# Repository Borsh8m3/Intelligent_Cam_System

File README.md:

# Intelligent Cam System

## Introduction
The Intelligent Cam System is a modular surveillance camera designed to operate in demanding weather conditions. It combines a rugged hardware platform—featuring 360° rotation, environmental sensors, and inductive control—with a Python-based video analytics pipeline powered by OpenCV and the `face_recognition` library. The system continuously monitors its surroundings, localises people, and reacts automatically to changes in temperature, humidity, and precipitation.

## Key Features
- **360° camera movement** – dual servos provide full panoramic motion along the horizontal and vertical axes.
- **Weather protection** – a sealed enclosure with anti-condensation heating and a rain-activated wiper keeps the optics clear.
- **Environmental monitoring** – temperature, humidity, dew point, and rain intensity are measured in real time.
- **Real-time video analytics** – faces are detected, recognised, and logged for later review; unknown faces can be labelled semi-automatically.
- **Communication module** – live video can be streamed to an external processing unit or monitoring dashboard.

## System Architecture
### Hardware Layer
- Weather-resistant housing with the camera mounted on a two-axis gimbal.
- Two servomotors to control pan and tilt.
- A DHT11 sensor that monitors enclosure temperature and humidity.
- An inductively powered rain sensor connected through an ADC input.
- A heater or fan that activates when the calculated dew point is exceeded.
- A servo-driven wiper that runs when rainfall is detected.

### Software Layer
- **Enclosure control (MicroPython)** – `Insidecode.py` ingests sensor data and orchestrates the servos, heater, and status LED.
- **Video analysis (Python)** – the `Video detection` module uses OpenCV to load known face encodings, perform detection, and annotate the live preview.
- **Face database management** – new frames tagged as `Unknown` are stored for later review, enabling incremental updates to the gallery of known users.

## Repository Structure
```
Intelligent_Cam_System/
├── code/
│   ├── Insidecode.py          # MicroPython control logic for the enclosure
│   └── Video detection/
│       ├── main_video.py      # Main loop for face detection and logging
│       └── simple_facerec.py  # Helper class for encoding and recognising faces
├── documents/                 # Project documentation and schematics
├── Photographic documentation # Prototype photos
├── Case/                      # CAD / 3D-print files for the enclosure
└── ...
```

## Requirements
### MicroPython Module
- A MicroPython-compatible microcontroller board (e.g. Raspberry Pi Pico).
- Libraries: `machine`, `servo`, `dht`, `utime`, `math`.
- Sensors wired to the pins defined in `Insidecode.py`.

### Video Analysis Module
- Python 3.9 or newer.
- Packages: `opencv-python`, `face_recognition`, `numpy`.
- UVC-compatible camera.
- An `images/` directory containing reference face photos (`.jpg`/`.png`).

Set up a virtual environment and install the Python dependencies:
```bash
python -m venv .venv
source .venv/bin/activate  # Windows: .venv\Scripts\activate
pip install -r requirements.txt  # Create the file based on the list above
```

## Usage
### Enclosure Module (MicroPython)
1. Upload `Insidecode.py` to the microcontroller.
2. Verify the peripherals are connected:
   - Servo (GPIO 0)
   - DHT11 sensor (GPIO 26)
   - Push button (GPIO 12)
   - Heater or relay output (GPIO 13)
   - Status LED (GPIO 25)
   - Rain sensor connected to ADC 27
3. Run the script. The heater activates once the dew point threshold is crossed, and the wiper engages when rain intensity rises above roughly 25% of the sensor’s range.

### Video Analysis and Face Recognition
1. Populate the `images/` directory with files named `First_Last.jpg`. Files starting with `Unknown` will be treated as new profiles.
2. Update the `encoding_folder` path in `main_video.py` so it points to the image directory on your machine.
3. Launch the application:
   ```bash
   python "code/Video detection"/main_video.py
   ```
4. The program opens the live preview, highlights recognised faces, and saves frames for unknown persons. After stopping the script you can rename the captured images to add them to the known gallery.

## Future Improvements
- Integrate with external alarm or IoT systems.
- Synchronise the face database between the edge device and a central server.
- Extend object detection to non-human entities (vehicles, animals, etc.).
- Monitor power supply health and report hardware diagnostics.

## License
This project is provided for educational use. Ensure you have the right to process the images of individuals in your face recognition workflow.

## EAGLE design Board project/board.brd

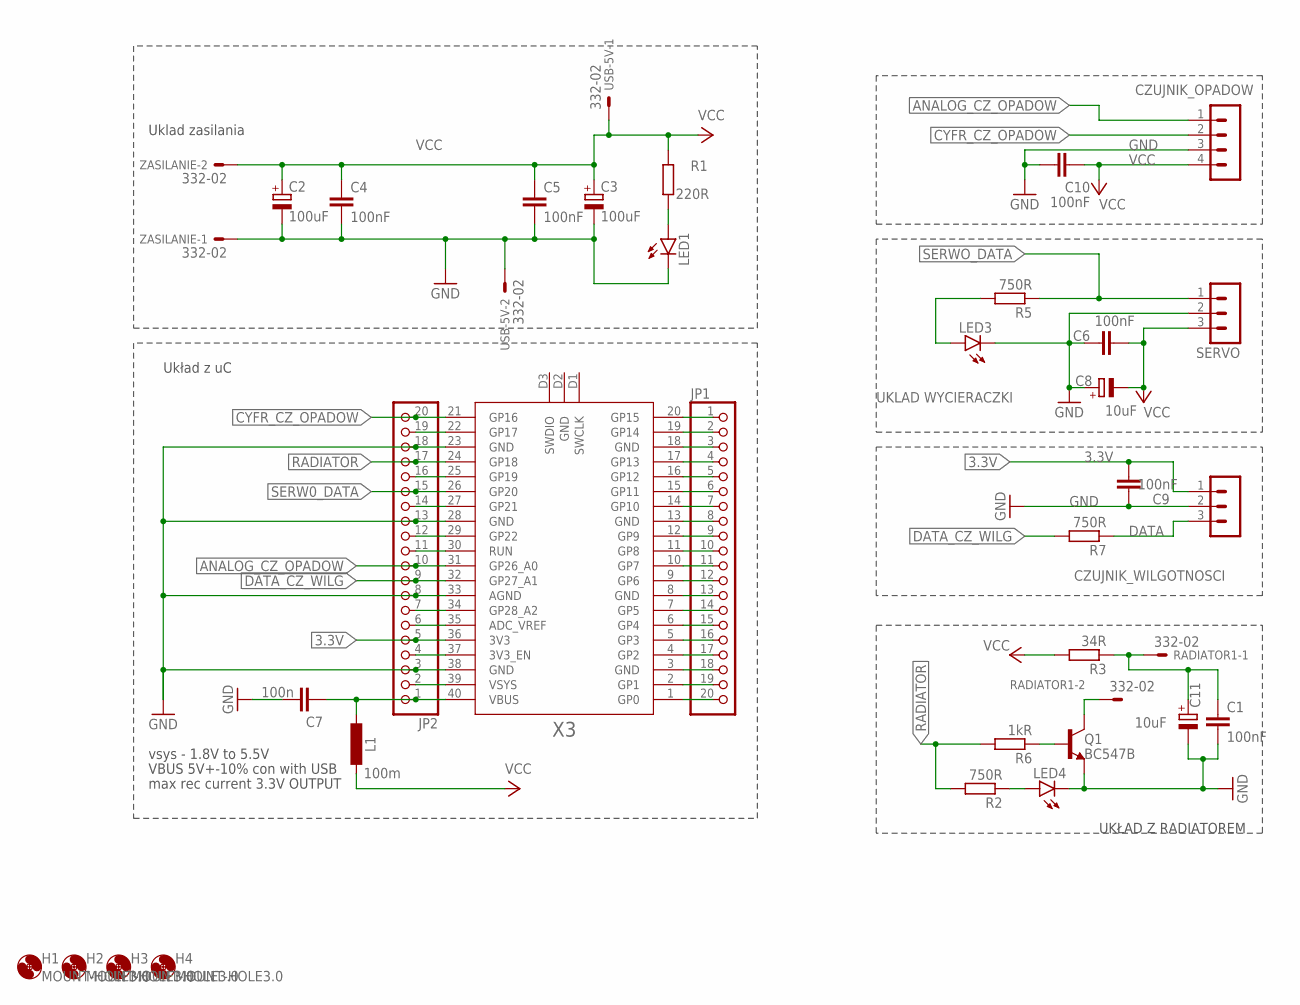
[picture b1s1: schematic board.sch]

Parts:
C1, C4, C5, C6, C9, C10: 100nF; C0805
C2, C3: 100uF; UD-5X5,8_NICHICON
C7: 100n; C0603
C8, C11: 10uF; E5-8,5
CZUJNIK_OPADOW: MA04-1
CZUJNIK_WILGOTNOSCI: MA03-1
H1, H2, H3, H4: MOUNT-HOLE3.0; 3,0
JP1, JP2: PINHD-1X20; 1X20
L1: 100m; L2012C
LED1, LED3, LED4: LEDSML0805; SML0805
Q1: BC547B; TO92
R1: 220R; R0805
R2, R5, R7: 750R; R0805
R3: 34R; R0805
R6: 1kR; R0805
RADIATOR1: 332-02
SERVO: MA03-1
USB-5V: 332-02
X3: RPI_PICO_IG-TH; RPI_PICO_TH
ZASILANIE: 332-02

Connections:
3.3V: C9.2, CZUJNIK_WILGOTNOSCI.1, JP2.5, X3.36 (3V3)
ANALOG_CZ_OPADOW: CZUJNIK_OPADOW.1, JP2.10, X3.31 (GP26_A0)
CYFR_CZ_OPADOW: CZUJNIK_OPADOW.2, JP2.20, X3.21 (GP16)
DATA: CZUJNIK_WILGOTNOSCI.3, R7.1
DATA_CZ_WILG: JP2.9, R7.2, X3.32 (GP27_A1)
GND: C1.2, C2.-, C3.-, C4.2, C5.2, C6.1, C7.2, C8.+, C9.1, C10.2, C11.-, CZUJNIK_OPADOW.3, CZUJNIK_WILGOTNOSCI.2, JP2.3, JP2.8, JP2.13, JP2.18, LED1.C, LED3.C, LED4.C, Q1.1 (E), SERVO.2, USB-5V.2, X3.23 (GND), X3.28 (GND), X3.33 (AGND), X3.38 (GND), ZASILANIE.1
unnamed: JP2.19, X3.22 (GP17)
unnamed: LED1.A, R1.2
unnamed: Q1.3 (C), RADIATOR1.2
unnamed: Q1.2 (B), R6.1
unnamed: C7.1, JP2.1, L1.2, X3.40 (VBUS)
unnamed: LED4.A, R2.1
unnamed: JP2.16, X3.25 (GP19)
unnamed: LED3.A, R5.2
unnamed: R5.1, SERVO.1
unnamed: JP1.1, X3.20 (GP15)
unnamed: JP2.14, X3.27 (GP21)
unnamed: JP2.12, X3.29 (GP22)
unnamed: JP2.11, X3.30 (RUN)
unnamed: JP2.7, X3.34 (GP28_A2)
unnamed: JP2.6, X3.35 (ADC_VREF)
unnamed: JP2.4, X3.37 (3V3_EN)
unnamed: JP1.20, X3.1 (GP0)
unnamed: JP1.19, X3.2 (GP1)
unnamed: JP1.18, X3.3 (GND)
unnamed: JP1.17, X3.4 (GP2)
unnamed: JP1.16, X3.5 (GP3)
unnamed: JP1.15, X3.6 (GP4)
unnamed: JP1.14, X3.7 (GP5)
unnamed: JP1.13, X3.8 (GND)
unnamed: JP1.12, X3.9 (GP6)
unnamed: JP1.11, X3.10 (GP7)
unnamed: JP1.10, X3.11 (GP8)
unnamed: JP1.9, X3.12 (GP9)
unnamed: JP1.8, X3.13 (GND)
unnamed: JP1.7, X3.14 (GP10)
unnamed: JP1.6, X3.15 (GP11)
unnamed: JP1.5, X3.16 (GP12)
unnamed: JP1.4, X3.17 (GP13)
unnamed: JP1.3, X3.18 (GND)
unnamed: JP1.2, X3.19 (GP14)
unnamed: JP2.2, X3.39 (VSYS)
RADIATOR: JP2.17, R2.2, R6.2, X3.24 (GP18)
SERW0_DATA: JP2.15, X3.26 (GP20)
VCC: C2.+, C3.+, C4.1, C5.1, C6.2, C8.-, C10.1, CZUJNIK_OPADOW.4, L1.1, R1.1, R3.2, SERVO.3, USB-5V.1, ZASILANIE.2
VCC1: C1.1, C11.+, R3.1, RADIATOR1.1

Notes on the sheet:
Uklad zasilania
Układ z uC
vsys - 1.8V to 5.5V
VBUS 5V+-10%
max rec current 3.3V OUTPUT
con with USB
UKŁAD Z RADIATOREM
UKLAD WYCIERACZKI

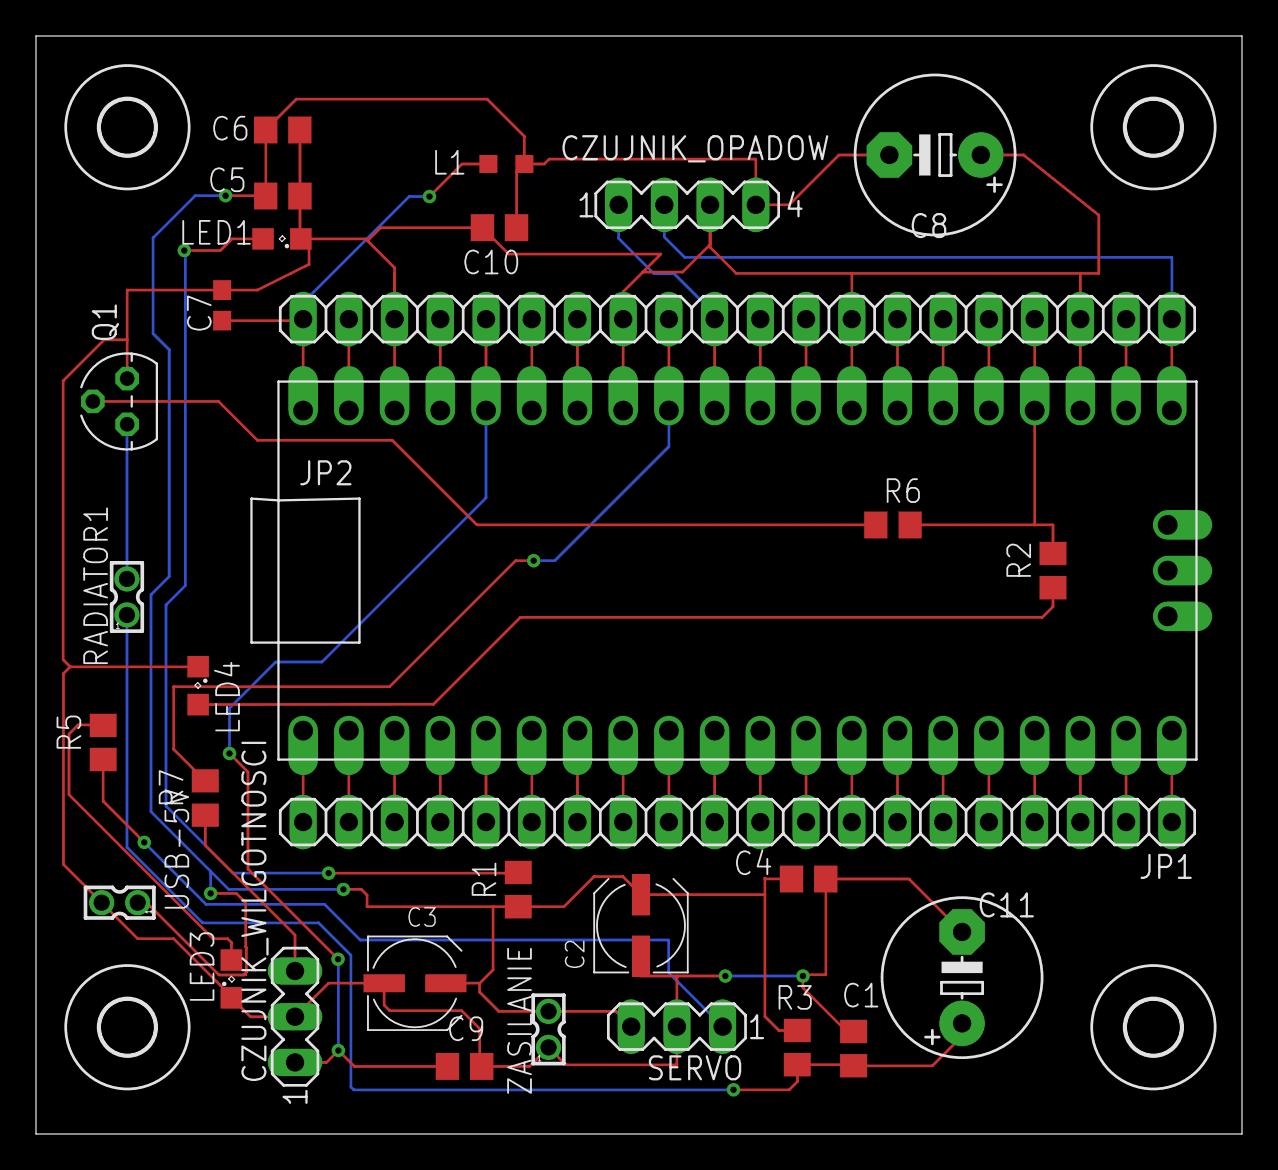
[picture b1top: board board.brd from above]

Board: 2 copper layers, 67.0 x 61.0 mm, 35 parts (0 on the bottom side), 46 nets.

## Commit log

2024-06-19 Big update 19.06
2024-06-19 Case update
2024-06-19 stp file
2024-06-20 newphoto
2024-06-23 board proj
2025-01-13 13.01
2025-10-23 docs: translate README to English
